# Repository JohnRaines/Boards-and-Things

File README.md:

# Boards-and-Things
Repository for boards and 3d printer files

Thermocouple board is a board small breakout board for 6 AD594 chips.

Probe wand is a snap together ring on  a stem for suspending boards

Probe jig is a stackable set of platforms for holding and powering boards

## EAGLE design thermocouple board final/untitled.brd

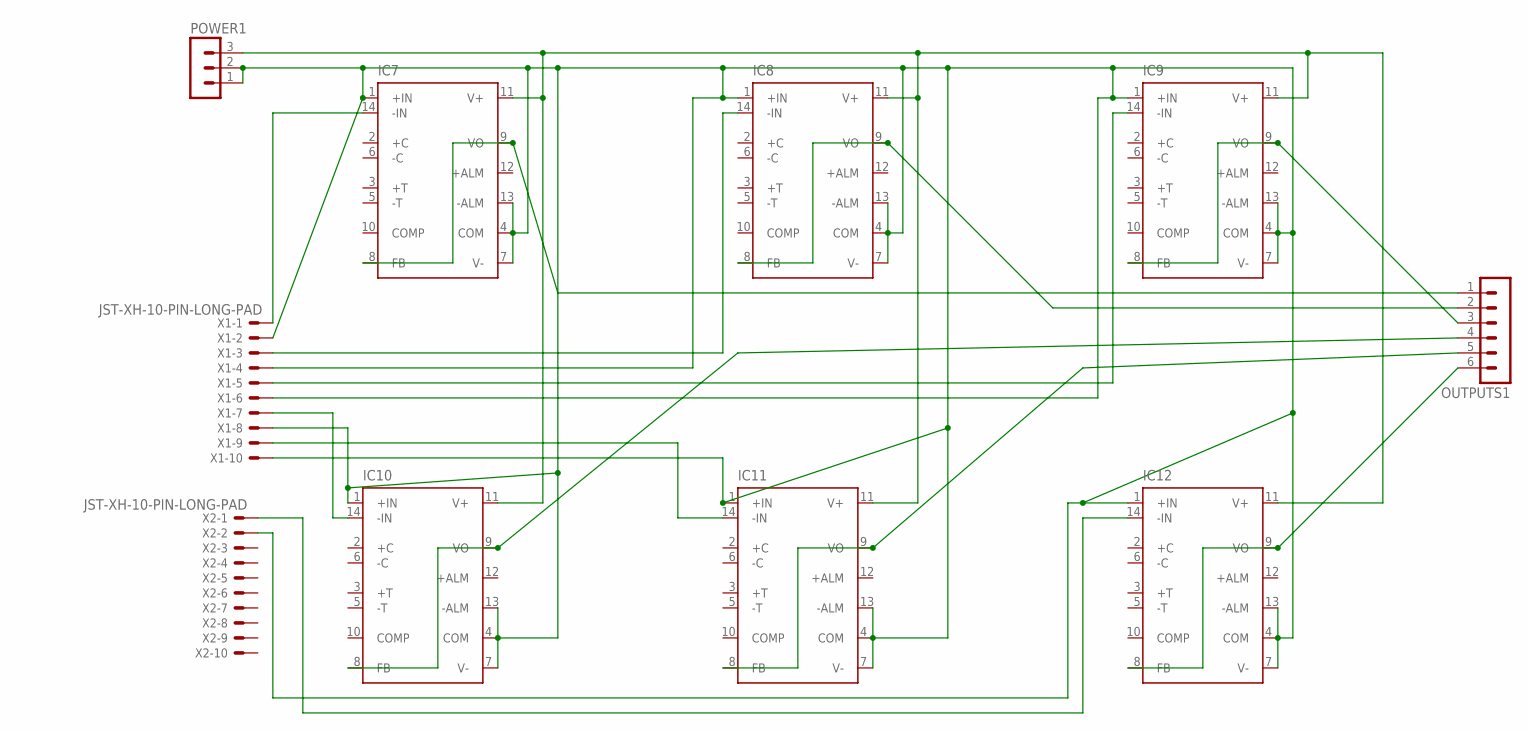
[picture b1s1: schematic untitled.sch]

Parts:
IC7, IC8, IC9, IC10, IC11, IC12: AD594; DIL14
OUTPUTS1: MA06-1
POWER1: MA03-1
X1, X2: JST-XH-10-PIN-LONG-PAD; JST-XH-10-PACKAGE-LONG-PAD

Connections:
unnamed: IC7.14 (-IN), X1.1
unnamed: IC8.14 (-IN), X1.3
unnamed: IC9.14 (-IN), X1.5
unnamed: IC7.1 (+IN), IC7.4 (COM), IC7.7 (V-), IC7.13 (-ALM), IC8.1 (+IN), IC8.4 (COM), IC8.7 (V-), IC8.13 (-ALM), IC9.1 (+IN), IC9.4 (COM), IC9.7 (V-), IC9.13 (-ALM), IC10.1 (+IN), IC10.4 (COM), IC10.7 (V-), IC10.13 (-ALM), IC11.1 (+IN), IC11.4 (COM), IC11.7 (V-), IC11.13 (-ALM), IC12.1 (+IN), IC12.4 (COM), IC12.7 (V-), IC12.13 (-ALM), POWER1.1, POWER1.2, X1.2, X1.4, X1.6, X1.8, X1.10, X2.2
unnamed: IC10.14 (-IN), X1.7
unnamed: IC11.14 (-IN), X1.9
unnamed: IC12.14 (-IN), X2.1
unnamed: IC7.8 (FB), IC7.9 (VO), OUTPUTS1.1
unnamed: IC8.8 (FB), IC8.9 (VO), OUTPUTS1.2
unnamed: IC9.8 (FB), IC9.9 (VO), OUTPUTS1.3
unnamed: IC10.8 (FB), IC10.9 (VO), OUTPUTS1.4
unnamed: IC11.8 (FB), IC11.9 (VO), OUTPUTS1.5
unnamed: IC12.8 (FB), IC12.9 (VO), OUTPUTS1.6
unnamed: IC7.11 (V+), IC8.11 (V+), IC9.11 (V+), IC10.11 (V+), IC11.11 (V+), IC12.11 (V+), POWER1.3

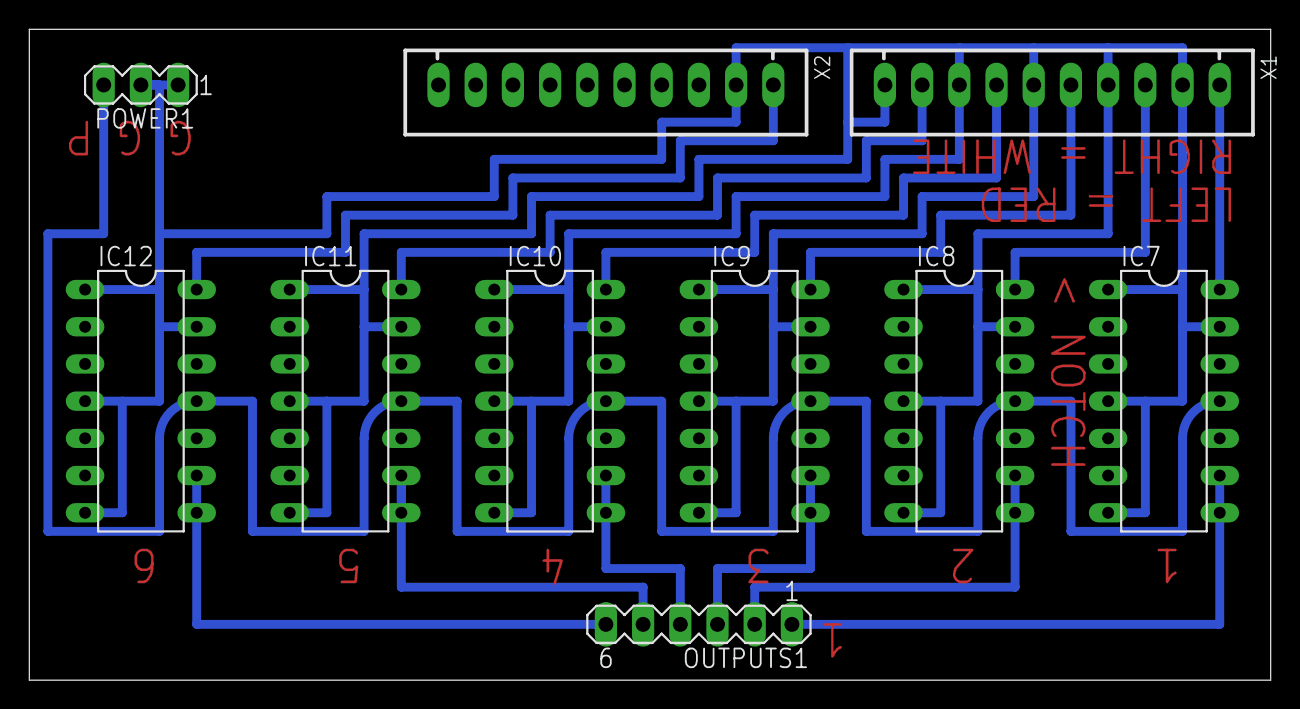
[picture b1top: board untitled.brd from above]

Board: 2 copper layers, 84.8 x 44.4 mm, 10 parts (0 on the bottom side), 14 nets.

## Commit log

2017-06-29 added thermocouple board
2017-06-30 3d printer files for probe holder
2017-06-30 added adapter for fitting wand to pvc pipe
2017-06-30 parts for building stackable jigs
2017-07-10 deck revision
    added post to support and power boards with buckets
2017-08-07 python code for tracking 3 coloured objects
    code detects a purple, a blue, and a green object. the blue and green objects define a square and the purple objects relative coordinates are displayed
2018-11-08 powered probe holder model files
    jig for holding and powering emote from usb.
    take 3 = main carriage
    mated back plate = what it says on the tin
    mounting hardware = piece that bonds to the usb A breakout board and attaches to underside of take 3
    assembly notes: copper tape is placed on contact sides of nub on take 3 to deliver power to the probe. solder wires to them and attached to the power terminals on the usb breakout, running the wire t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
